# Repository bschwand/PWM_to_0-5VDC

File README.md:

# PWM_to_0-5VDC
a simple PWM to 0-5VDC analog interface. Meant to interface BLDC hair dryer fan to 3Dprinter 12V fan output.
All information, motivation, description https://blog.tinkerbox.org/3d-print/PWM_to_0-5VDC/

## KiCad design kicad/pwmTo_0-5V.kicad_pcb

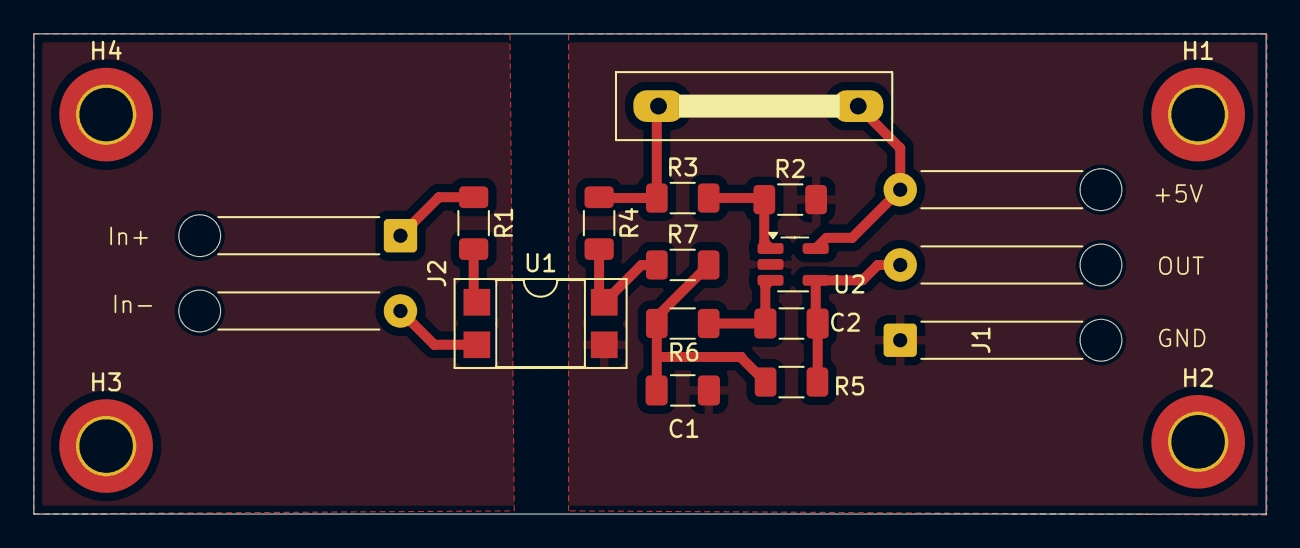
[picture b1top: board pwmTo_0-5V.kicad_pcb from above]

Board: 2 copper layers, 73.7 x 28.7 mm, 18 parts (0 on the bottom side), 10 nets.

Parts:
C1: 100nF; C_1206_3216Metric_Pad1.33x1.80mm_HandSolder
C2: 68nF; C_1206_3216Metric_Pad1.33x1.80mm_HandSolder
H1, H2, H3, H4: MountingHole_Pad_MP; MountingHole_3.2mm_M3_DIN965_Pad_TopOnly
J1: Conn_01x03_Socket; SolderWire-0.25sqmm_1x03_P4.5mm_D0.65mm_OD2mm_Relief
J2: Conn_01x02_Socket; SolderWire-0.25sqmm_1x02_P4.5mm_D0.65mm_OD2mm_Relief
JP1: Jumper_2_Bridged; Jumper-Wire_12mm_Blue
R1: 550; R_1206_3216Metric_Pad1.30x1.75mm_HandSolder
R2, R3: 100k; R_1206_3216Metric_Pad1.30x1.75mm_HandSolder
R4: 1k; R_1206_3216Metric_Pad1.30x1.75mm_HandSolder
R5, R7: 150k; R_1206_3216Metric_Pad1.30x1.75mm_HandSolder
R6: 82k; R_1206_3216Metric_Pad1.30x1.75mm_HandSolder
U1: EL817; DIP-4_W7.62mm_SMDSocket_SmallPads
U2: LMV321; SOT-23-5_HandSoldering

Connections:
GND: C1.2, J1.1, R2.2, U1.3, U2.2 (V-)
unnamed: C1.1, R5.1, R6.1, R7.2
unnamed: C2.2, J1.2, R5.2, U2.4
unnamed: J2.1, R1.1
unnamed: J2.2, U1.2
unnamed: R1.2, U1.1
unnamed: R4.2, R7.1, U1.4
unnamed: R2.1, R3.2, U2.1 (+)
unnamed: C2.1, R6.2, U2.3 (-)
VCC: J1.3, JP1.1 (A), JP1.2 (B), R3.1, R4.1, U2.5 (V+)

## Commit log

2025-02-04 add link to blog article
2025-02-04 update schematic legend
